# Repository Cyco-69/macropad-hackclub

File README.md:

# Macropad-Hackclub
A 3 by 3 macropad keyboard layout with a rotary volume knob and a small OLED display mounted on a custom PCB. The display I used is the SD1306 128 by 32  OLED.
## Schematic

## PCB-Design

### ⚠️ Future consideration: 
- May need to change the Micro Controller to an ESP32 Dev kit
- May need to replace the OLED to the 0.6' 128 by 64 version
- May also need to change the keys

> **Note:** WTH everything may need to be replaced except for the knob I hope I may also use prototype pcb instead of a proffesional if I am unable to get the funds

[schematic]: Images/schematic.png
[pcb]: Images/PCB_RP2040.png

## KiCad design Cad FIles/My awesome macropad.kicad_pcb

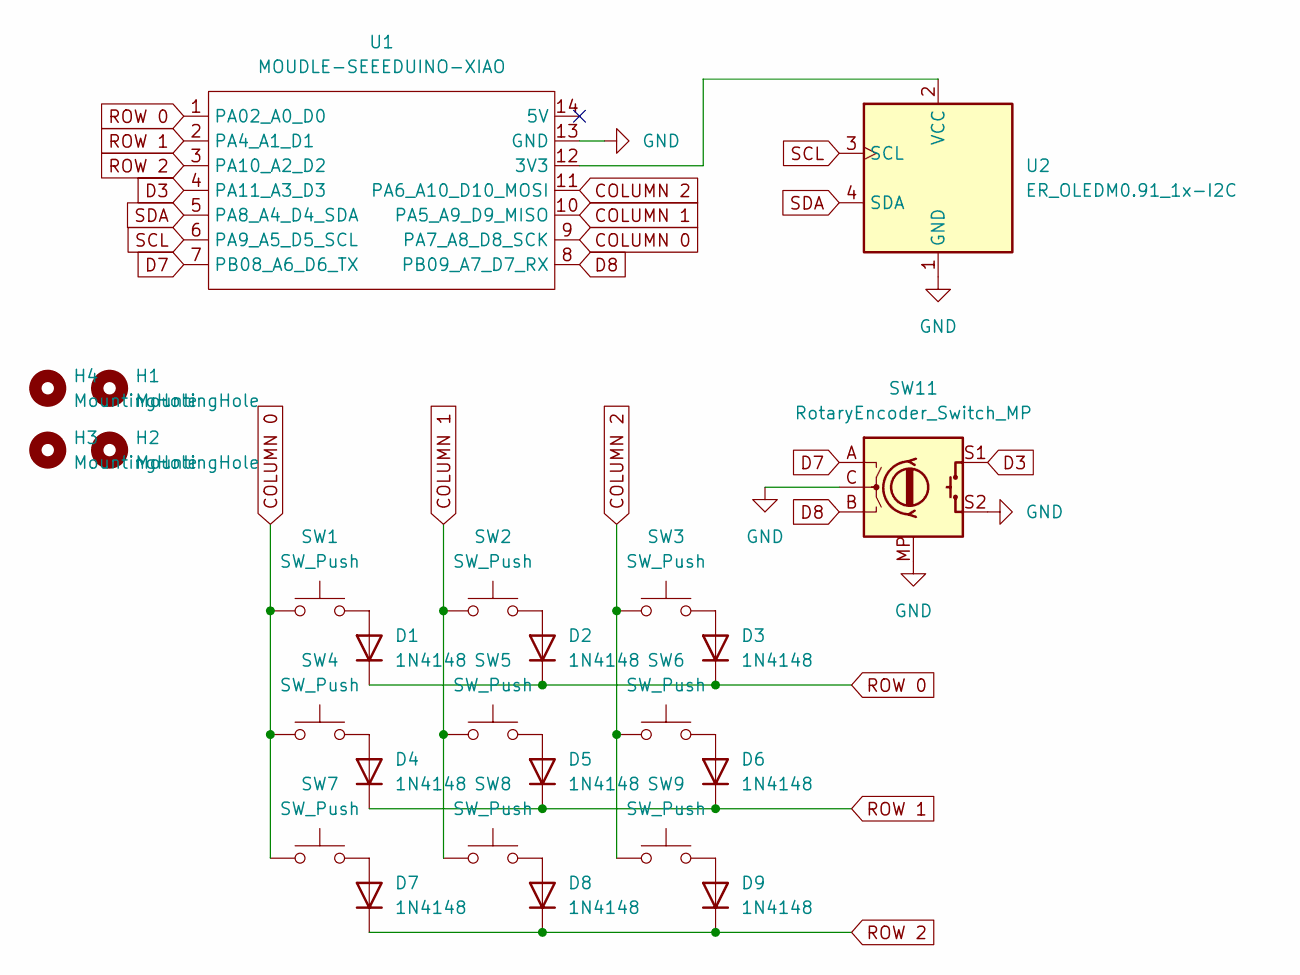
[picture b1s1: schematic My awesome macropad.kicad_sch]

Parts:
D1, D2, D3, D4, D5, D6, D7, D8, D9: 1N4148; D_DO-35_SOD27_P7.62mm_Horizontal
H1, H2, H3, H4: MountingHole; MountingHole_3.2mm_M3
SW1, SW2, SW3, SW4, SW5, SW6, SW7, SW8, SW9: SW_Push; SW_Cherry_MX_1.00u_PCB
SW11: RotaryEncoder_Switch_MP; RotaryEncoder_Alps_EC11E-Switch_Vertical_H20mm_CircularMoun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
U1: MOUDLE-SEEEDUINO-XIAO; XIAO-Generic-Hybrid-14P-2.54-21X17.8MM
U2: ER_OLEDM0.91_1x-I2C

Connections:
COLUMN 0: SW1.1, SW4.1, SW7.1, U1.9 (PA7_A8_D8_SCK)
COLUMN 1: SW2.1, SW5.1, SW8.1, U1.10 (PA5_A9_D9_MISO)
COLUMN 2: SW3.1, SW6.1, SW9.1, U1.11 (PA6_A10_D10_MOSI)
D3: SW11.S1, U1.4 (PA11_A3_D3)
D7: SW11.A, U1.7 (PB08_A6_D6_TX)
D8: SW11.B, U1.8 (PB09_A7_D7_RX)
GND: SW11.C, SW11.MP, SW11.S2, U1.13 (GND), U2.1 (GND)
unnamed: D1.2 (A), SW1.2
unnamed: D2.2 (A), SW2.2
unnamed: D3.2 (A), SW3.2
unnamed: D4.2 (A), SW4.2
unnamed: D5.2 (A), SW5.2
unnamed: D6.2 (A), SW6.2
unnamed: D7.2 (A), SW7.2
unnamed: D8.2 (A), SW8.2
unnamed: D9.2 (A), SW9.2
unnamed: U1.12 (3V3), U2.2 (VCC)
ROW 0: D1.1 (K), D2.1 (K), D3.1 (K), U1.1 (PA02_A0_D0)
ROW 1: D4.1 (K), D5.1 (K), D6.1 (K), U1.2 (PA4_A1_D1)
ROW 2: D7.1 (K), D8.1 (K), D9.1 (K), U1.3 (PA10_A2_D2)
SCL: U1.6 (PA9_A5_D5_SCL), U2.3 (SCL)
SDA: U1.5 (PA8_A4_D4_SDA), U2.4 (SDA)

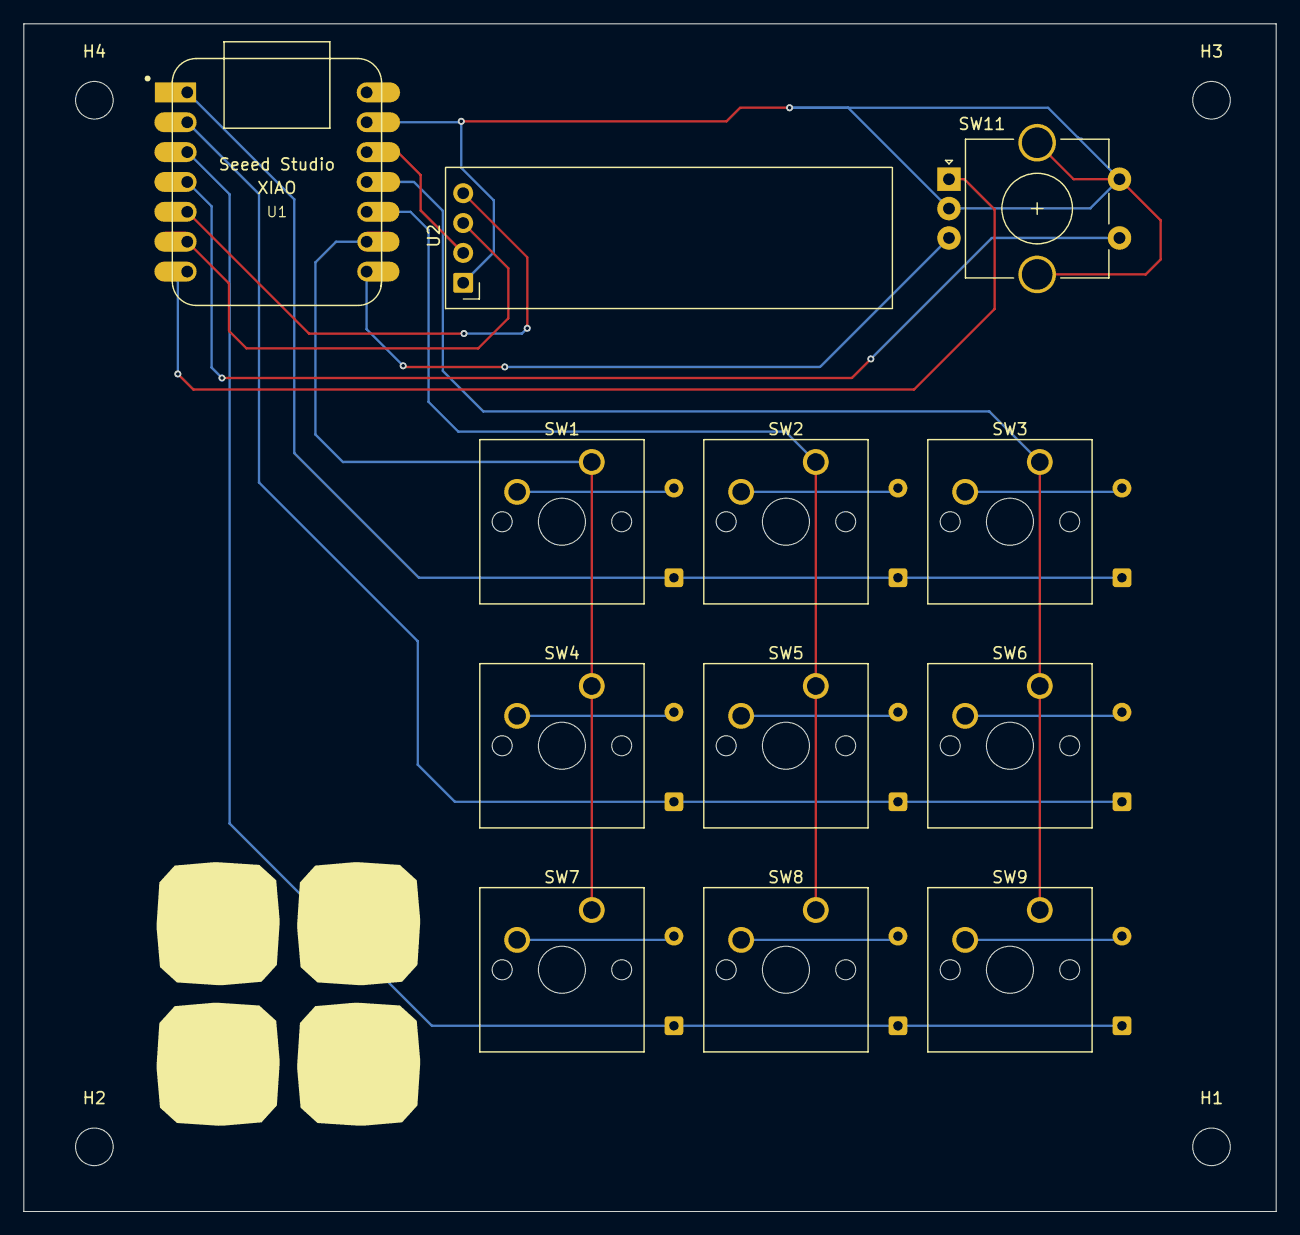
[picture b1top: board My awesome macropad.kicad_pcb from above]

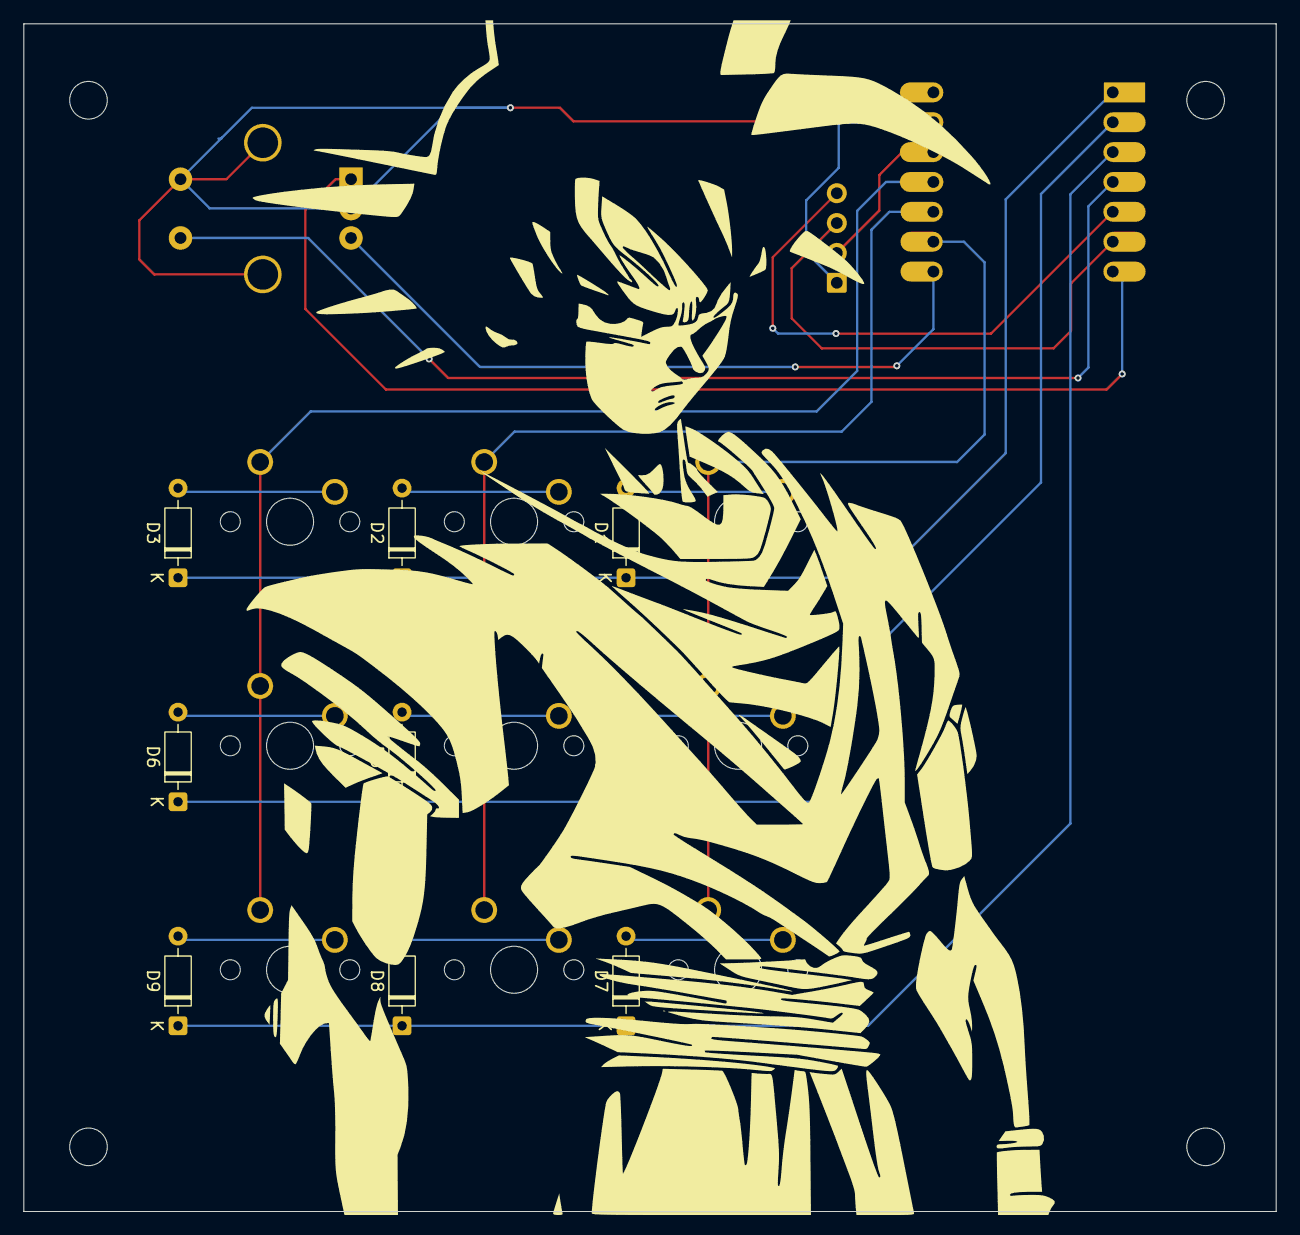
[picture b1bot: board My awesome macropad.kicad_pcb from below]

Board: 2 copper layers, 106.5 x 101.0 mm, 25 parts (9 on the bottom side), 22 nets.

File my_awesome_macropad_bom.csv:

Designator,Footprint,Quantity,Value,LCSC Part #
"D1, D2, D3, D4, D5, D6, D7, D8, D9",D_DO-35_SOD27_P7.62mm_Horizontal,9,1N4148,
"SW1, SW2, SW3, SW4, SW5, SW6, SW7, SW8, SW9",SW_Cherry_MX_1.00u_PCB,9,SW_Push,
SW11,RotaryEncoder_Alps_EC11E-Switch_Vertical_H20mm_CircularMountingHoles,1,RotaryEncoder_Switch_MP,
U1,XIAO-Generic-Hybrid-14P-2.54-21X17.8MM,1,MOUDLE-SEEEDUINO-XIAO,
U2,ER_OLEDM0.91_1x-I2C,1,ER_OLEDM0.91_1x-I2C,
